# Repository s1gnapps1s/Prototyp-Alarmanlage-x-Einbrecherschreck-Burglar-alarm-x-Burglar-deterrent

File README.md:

## Deutsch
Dieses Repository enthält alle notwendigen Unterlagen für den Hardware-Aufbau:
- **Schaltpläne** (Schematics)
- **Lötpläne** (Soldering layouts)
- **Beispielbilder** für das Gehäuse und den Zusammenbau

**Hinweis zum Quellcode:**
Der zugehörige Programmcode ist in diesem Repository nicht öffentlich enthalten. Er ist jedoch auf Anfrage verfügbar. Bei Interesse oder Fragen zum Projekt schreib mir bitte eine Private Nachricht (PM).

## ⚠️ Wichtige Sicherheitshinweise 
---
* **Kein zertifiziertes System:** Dieses Projekt dient ausschließlich Bildungs- und Hobbyzwecken. Es ist **kein Ersatz** für eine professionelle, zertifizierte Alarmanlage. Der Autor garantiert nicht für die Funktion im Ernstfall.
* **Haftung:** Die Nutzung und der Nachbau erfolgen auf eigene Gefahr. Der Autor übernimmt keine Haftung für Sachschäden (z. B. durch Einbruch oder Fehlfunktion) oder Personenschäden.
* **Elektronik-Sicherheit:** Achten Sie beim Löten und Aufbau auf gängige Sicherheitsstandards. Arbeiten an elektrischen Bauteilen können bei unsachgemäßer Handhabung gefährlich sein.
---

## English
This repository contains all documentation required for the hardware assembly:
- **Schematics**
- **Soldering plans**
- **Example images** for the enclosure and assembly

**Note on Source Code:**
The corresponding source code is not publicly available in this repository. However, it is available upon request. If you are interested or have questions regarding the project, please feel free to send me a private message (PM).

## ⚠️ Important Safety Information
---
* **No Certified System:** This project is for educational and hobbyist purposes only. It is **not a substitute** for a professional, certified security system. The author does not guarantee its functionality in emergency situations.
* **Liability:** Use and assembly are at your own risk. The author assumes no liability for property damage (e.g., due to burglary or malfunction) or personal injury.
* **Electronics Safety:** Follow standard safety protocols during soldering and assembly. Working with electronic components can be dangerous if handled improperly.

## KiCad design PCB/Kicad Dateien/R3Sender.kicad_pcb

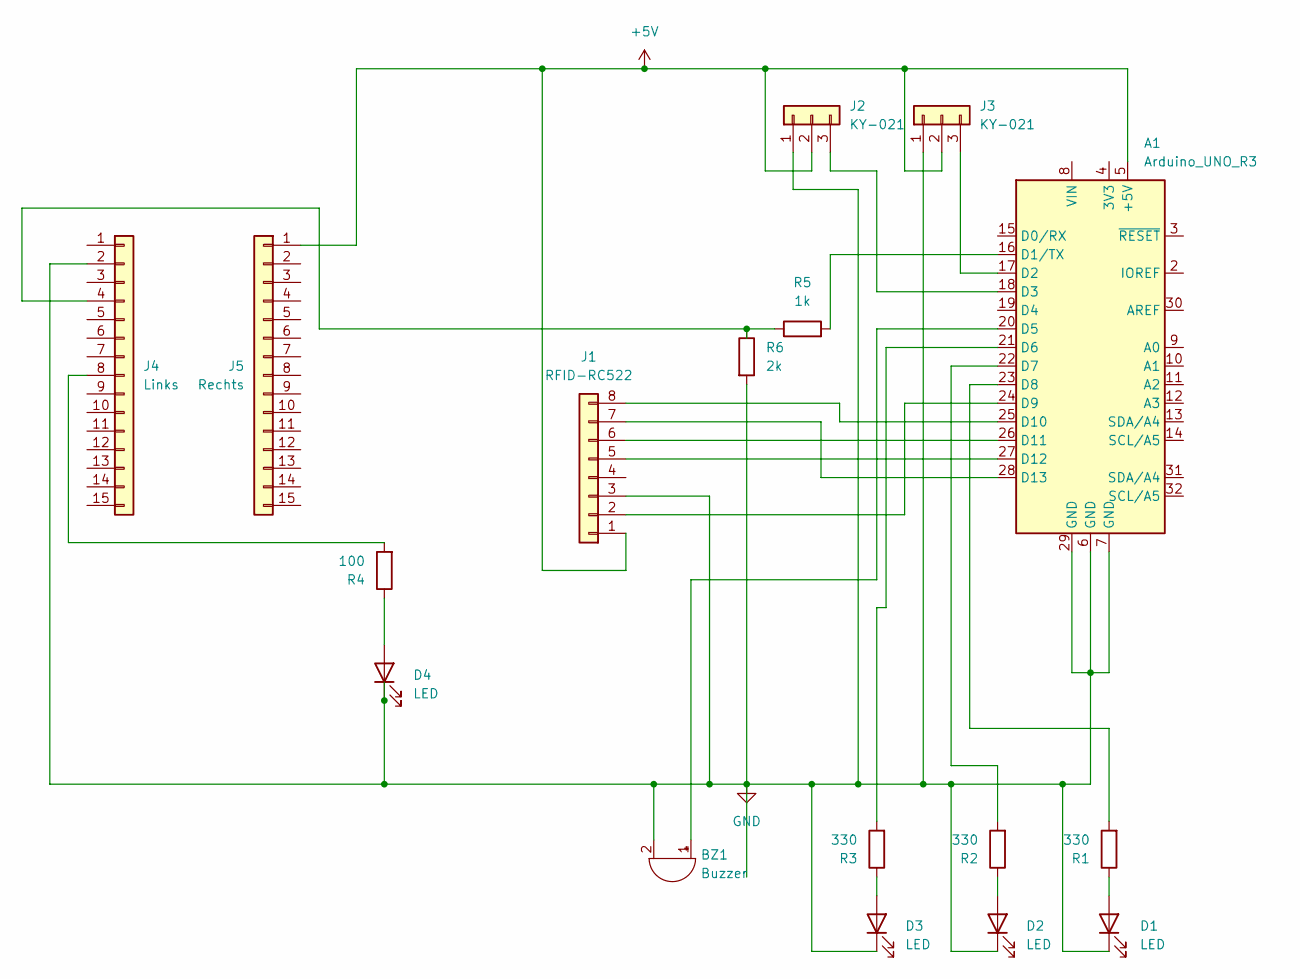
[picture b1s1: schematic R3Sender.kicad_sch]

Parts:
A1: Arduino_UNO_R3
BZ1: Buzzer; PinHeader_1x02_P2.54mm_Vertical
D1, D2, D3, D4: LED; LED_D5.0mm
J1: RFID-RC522; PinHeader_1x08_P2.54mm_Vertical
J2, J3: KY-021; PinHeader_1x03_P2.54mm_Vertical
J4: Links; PinHeader_1x15_P2.54mm_Vertical
J5: Rechts; PinHeader_1x15_P2.54mm_Vertical
R1, R2, R3: 330; R_Axial_DIN0207_L6.3mm_D2.5mm_P7.62mm_Horizontal
R4: 100; R_Axial_DIN0207_L6.3mm_D2.5mm_P7.62mm_Horizontal
R5: 1k; R_Axial_DIN0207_L6.3mm_D2.5mm_P7.62mm_Horizontal
R6: 2k; R_Axial_DIN0207_L6.3mm_D2.5mm_P7.62mm_Horizontal

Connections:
+5V: A1.5 (+5V), J1.1, J2.2, J3.2, J5.1
GND: A1.6 (GND), A1.7 (GND), A1.29 (GND), BZ1.2 (-), D1.1 (K), D2.1 (K), D3.1 (K), D4.1 (K), J1.3, J2.1, J3.1, J4.2, R6.2
unnamed: A1.16 (D1/TX), R5.2
unnamed: A1.17 (D2), J3.3
unnamed: A1.18 (D3), J2.3
unnamed: A1.20 (D5), BZ1.1 (+)
unnamed: A1.21 (D6), R3.2
unnamed: A1.22 (D7), R2.2
unnamed: A1.23 (D8), R1.2
unnamed: A1.24 (D9), J1.2
unnamed: A1.25 (D10), J1.8
unnamed: A1.26 (D11), J1.6
unnamed: A1.27 (D12), J1.5
unnamed: A1.28 (D13), J1.7
unnamed: D1.2 (A), R1.1
unnamed: D2.2 (A), R2.1
unnamed: D3.2 (A), R3.1
unnamed: D4.2 (A), R4.1
unnamed: J4.4, R5.1, R6.1
unnamed: J4.8, R4.2

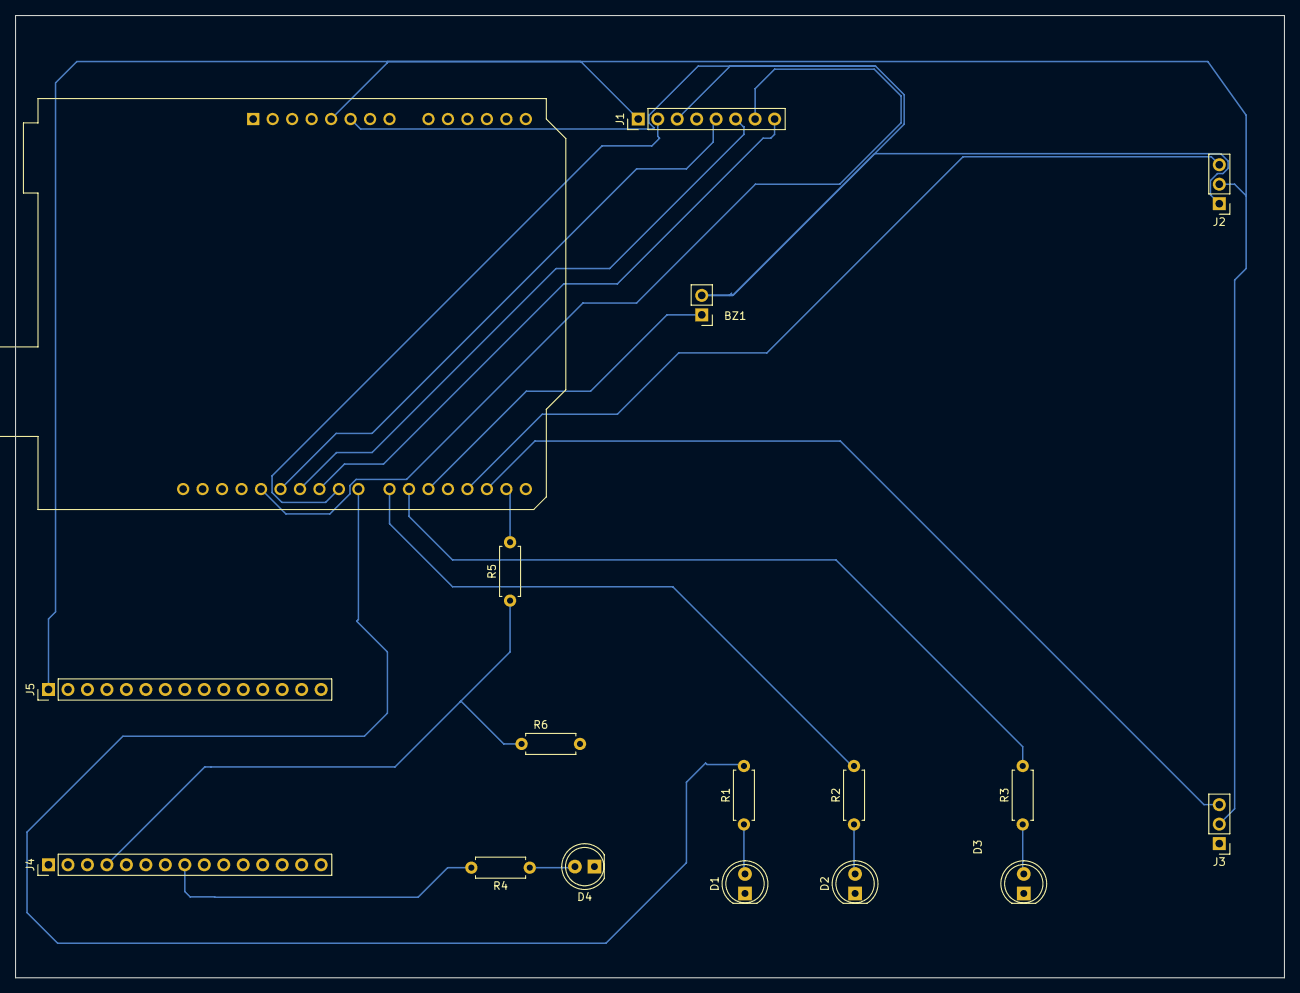
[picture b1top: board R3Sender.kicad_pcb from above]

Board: 2 copper layers, 165.5 x 125.5 mm, 17 parts (0 on the bottom side), 20 nets.

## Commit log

2025-12-29 LICENSE.md
2025-12-29 READMEfirst.md
2025-12-29 README _first.md
2025-12-29 Rename READMEfirst.md to README.md
2026-01-02 Add ESP8266 setup guide
    This document provides a step-by-step guide on flashing and configuring the ESP8266, including WLAN and IP settings.
